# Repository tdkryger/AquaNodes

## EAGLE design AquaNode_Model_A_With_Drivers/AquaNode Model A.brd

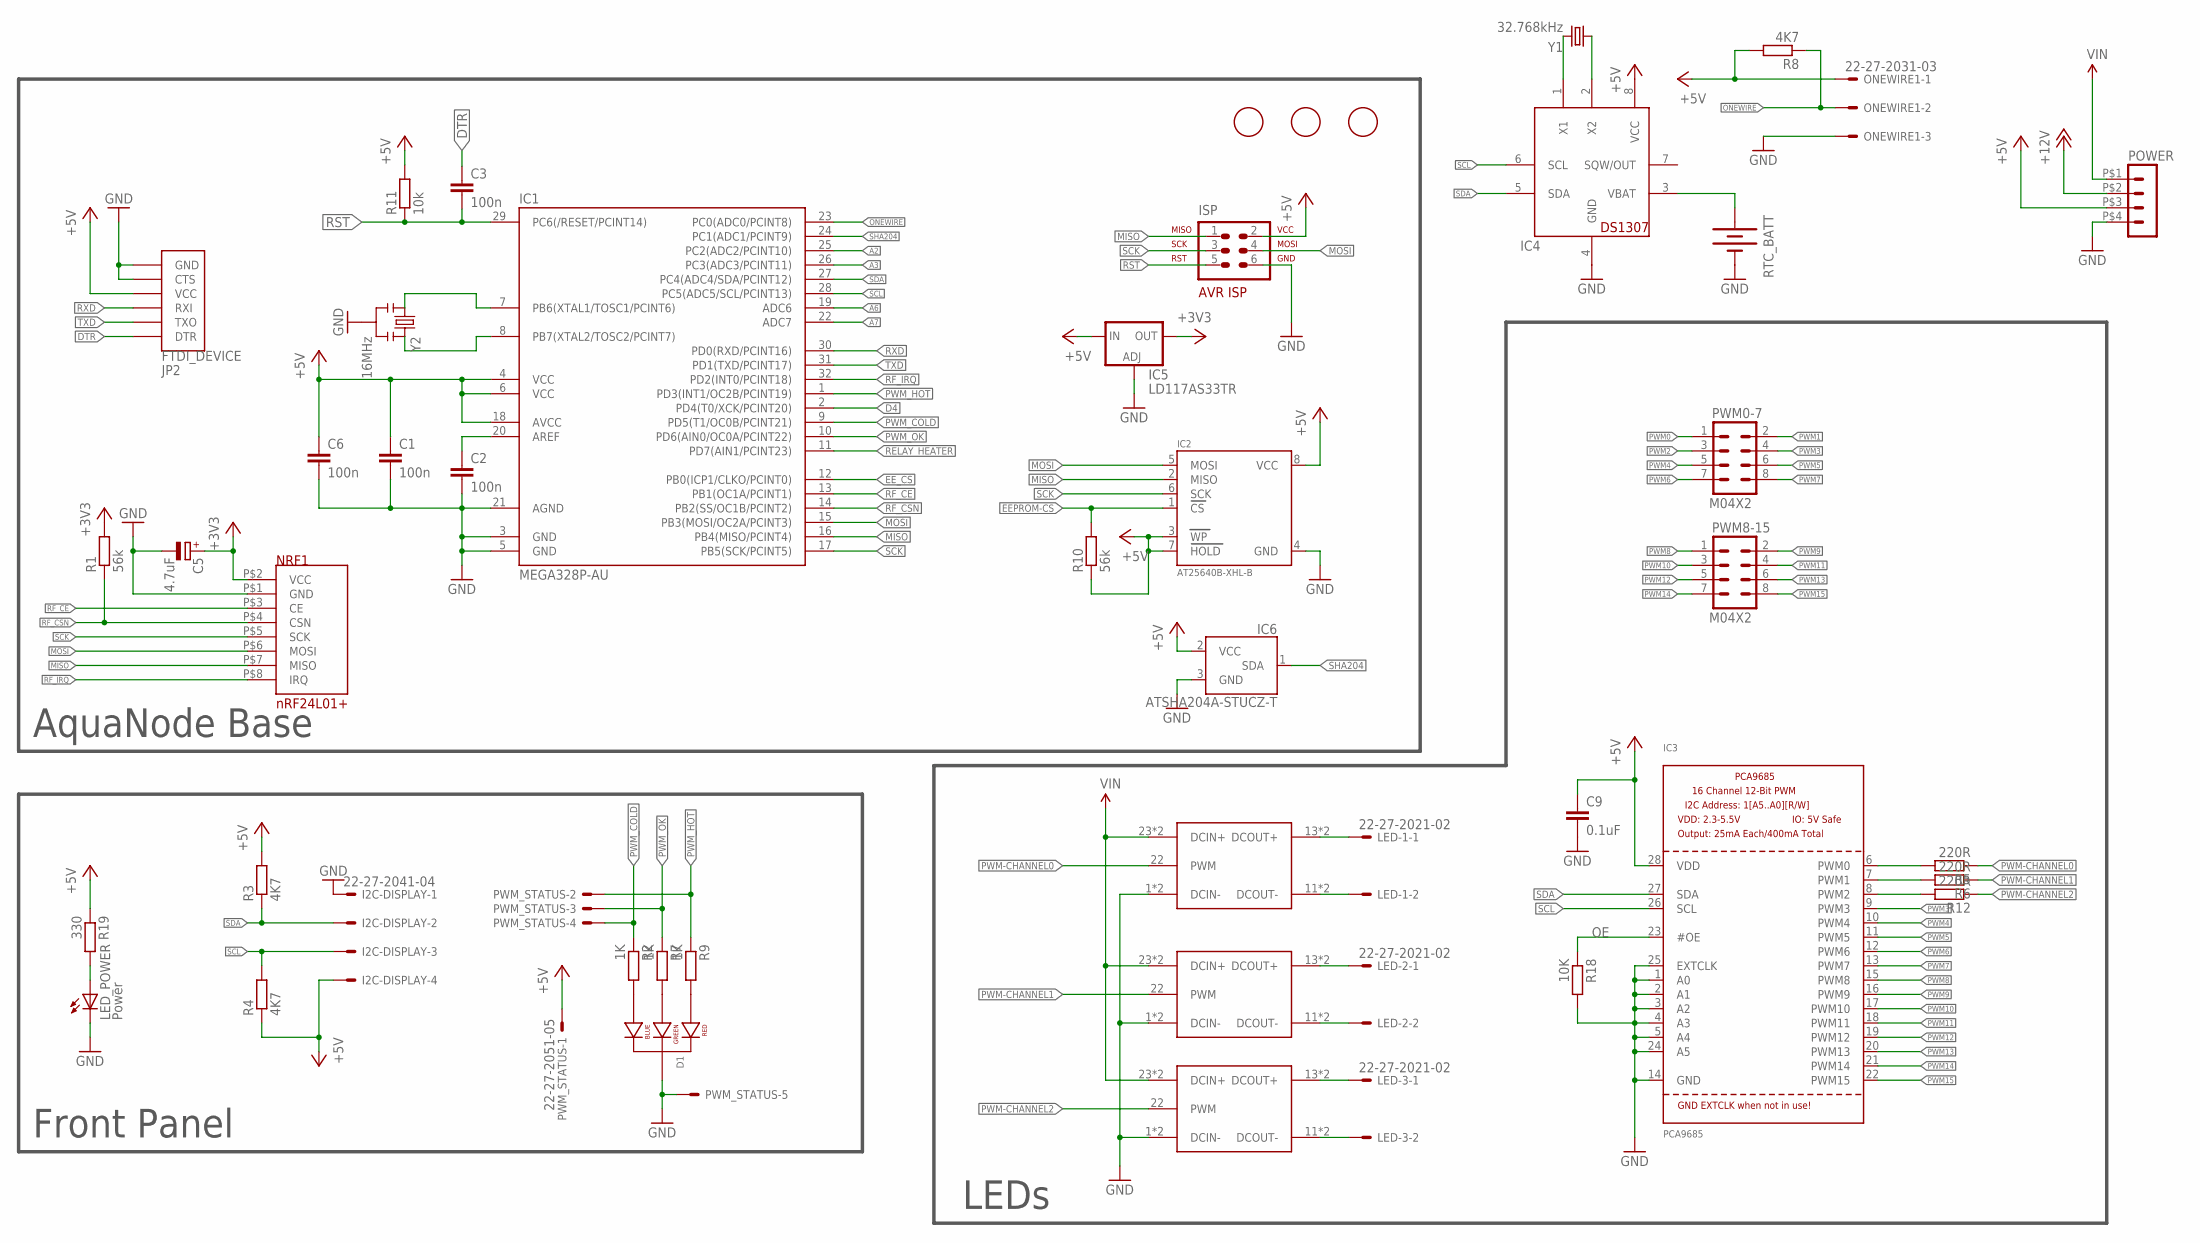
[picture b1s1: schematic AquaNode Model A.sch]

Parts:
C1, C2, C3, C6: 100n; C0603
C5: 4.7uF; E2,5-6
C9: 0.1uF; C0805
D1: LED-RGB-CC; LED-RGB-THRU
DRV1, DRV2, DRV3: DLL-XXXH; LDD_H
FID1, FID2, FID3: FIDUCIAL; FIDUCIAL_1MM
I2C-DISPLAY: 22-27-2041-04; 6410-04
IC1: MEGA328P-AU; TQFP32-08
IC2: AT25640B-XHL-B; TSSOP8-4.4MM
IC3: PCA9685; TSSOP28
IC4: DS1307; SO08
IC5: LD117AS33TR; SOT223
IC6: ATSHA204A-STUCZ-T; SOT23-3
ISP: ISP; AVR-ISP-6
JP2: FTDI_DEVICE; FTDI_DEVICE_SIDE
LED-1, LED-2, LED-3: 22-27-2021-02; 6410-02
LED_POWER: Power; LED3MM
NRF1: NRF24L01+.EBAY
ONEWIRE1: 22-27-2031-03; 6410-03
POWER: HEADER_POS4_43045-0412; 43045-0412
PWM0-7, PWM8-15: M04X2; 2X4
PWM_STATUS: 22-27-2051-05; 6410-05
R1, R10: 56k; M0805
R2, R7, R9: 1K; M0805
R3, R4, R8: 4K7; M0805
R5, R6, R12: 220R; M0805
R11: 10k; R0603
R18: 10K; M0805
R19: 330; M0805
RTC_BATT: BATTERY20SMD; BATTCON_20MM
Y1: 32.768kHz; CRYSTAL-32KHZ-SMD
Y2: 16MHz; RESONATOR-PTH

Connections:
+3V3: C5.+, IC5.4 (OUT), NRF1.P$2 (VCC), R1.2
+5V: C1.1, C6.1, C9.1, I2C-DISPLAY.4, IC1.4 (VCC), IC1.6 (VCC), IC1.18 (AVCC), IC2.3 (WP), IC2.7 (HOLD), IC2.8 (VCC), IC3.28 (VDD), IC4.8 (VCC), IC5.3 (IN), IC6.2 (VCC), ISP.2, JP2.P$4 (VCC), ONEWIRE1.1, POWER.P$3 (3), PWM_STATUS.1, R3.2, R4.1, R8.2, R10.1, R11.2, R19.1
+12V: POWER.P$2 (2)
A2: IC1.25 (PC2(ADC2/PCINT10))
A3: IC1.26 (PC3(ADC3/PCINT11))
A6: IC1.19 (ADC6)
A7: IC1.22 (ADC7)
D4: IC1.2 (PD4(T0/XCK/PCINT20))
DTR: C3.1, JP2.P$1 (DTR)
EEPROM-CS: IC2.1 (CS), R10.2
EE_CS: IC1.12 (PB0(ICP1/CLKO/PCINT0))
GND: C1.2, C2.2, C5.-, C6.2, C9.2, D1.2 (CATHODE), DRV1.1 (DCIN-), DRV1.2 (DCIN-), DRV2.1 (DCIN-), DRV2.2 (DCIN-), DRV3.1 (DCIN-), DRV3.2 (DCIN-), I2C-DISPLAY.1, IC1.3 (GND), IC1.5 (GND), IC1.21 (AGND), IC2.4 (GND), IC3.1 (A0), IC3.2 (A1), IC3.3 (A2), IC3.4 (A3), IC3.5 (A4), IC3.14 (GND), IC3.24 (A5), IC3.25 (EXTCLK), IC4.4 (GND), IC5.1 (ADJ), IC6.3 (GND), ISP.6, JP2.P$5 (CTS), JP2.P$6 (GND), LED_POWER.K (C), NRF1.P$1 (GND), ONEWIRE1.3, POWER.P$4 (4), PWM_STATUS.5, R18.2, RTC_BATT.2 (-), Y2.2
LED+1: DRV1.13 (DCOUT+), DRV1.14 (DCOUT+), LED-1.1
LED+2: DRV2.13 (DCOUT+), DRV2.14 (DCOUT+), LED-2.1
LED+3: DRV3.13 (DCOUT+), DRV3.14 (DCOUT+), LED-3.1
MISO: IC1.16 (PB4(MISO/PCINT4)), IC2.2 (MISO), ISP.1, NRF1.P$7 (MISO)
MOSI: IC1.15 (PB3(MOSI/OC2A/PCINT3)), IC2.5 (MOSI), ISP.4, NRF1.P$6 (MOSI)
unnamed: D1.4 (BLUE_CATHODE), R2.2
unnamed: D1.3 (GREEN_CATHODE), R7.2
unnamed: D1.1 (RED_CATHODE), R9.2
unnamed: C2.1, IC1.20 (AREF)
unnamed: IC4.3 (VBAT), RTC_BATT.1 (+)
unnamed: IC4.1 (X1), Y1.X2 (2)
unnamed: IC4.2 (X2), Y1.X1 (1)
unnamed: IC1.7 (PB6(XTAL1/TOSC1/PCINT6)), Y2.1
unnamed: IC1.8 (PB7(XTAL2/TOSC2/PCINT7)), Y2.3
unnamed: DRV1.11 (DCOUT-), DRV1.12 (DCOUT-), LED-1.2
unnamed: DRV2.11 (DCOUT-), DRV2.12 (DCOUT-), LED-2.2
unnamed: DRV3.11 (DCOUT-), DRV3.12 (DCOUT-), LED-3.2
unnamed: LED_POWER.A, R19.2
OE: IC3.23 (#OE), R18.1
ONEWIRE: IC1.23 (PC0(ADC0/PCINT8)), ONEWIRE1.2, R8.1
PWM0: IC3.6 (PWM0), PWM0-7.1, R5.2
PWM1: IC3.7 (PWM1), PWM0-7.2, R6.2
PWM2: IC3.8 (PWM2), PWM0-7.3, R12.2
PWM3: IC3.9 (PWM3), PWM0-7.4
PWM4: IC3.10 (PWM4), PWM0-7.5
PWM5: IC3.11 (PWM5), PWM0-7.6
PWM6: IC3.12 (PWM6), PWM0-7.7
PWM7: IC3.13 (PWM7), PWM0-7.8
PWM8: IC3.15 (PWM8), PWM8-15.1
PWM9: IC3.16 (PWM9), PWM8-15.2
PWM10: IC3.17 (PWM10), PWM8-15.3
PWM11: IC3.18 (PWM11), PWM8-15.4
PWM12: IC3.19 (PWM12), PWM8-15.5
PWM13: IC3.20 (PWM13), PWM8-15.6
PWM14: IC3.21 (PWM14), PWM8-15.7
PWM15: IC3.22 (PWM15), PWM8-15.8
PWM-CHANNEL0: DRV1.22 (PWM), R5.1
PWM-CHANNEL1: DRV2.22 (PWM), R6.1
PWM-CHANNEL2: DRV3.22 (PWM), R12.1
PWM_COLD: IC1.9 (PD5(T1/OC0B/PCINT21)), PWM_STATUS.4, R2.1
PWM_HOT: IC1.1 (PD3(INT1/OC2B/PCINT19)), PWM_STATUS.2, R9.1
PWM_OK: IC1.10 (PD6(AIN0/OC0A/PCINT22)), PWM_STATUS.3, R7.1
RELAY_HEATER: IC1.11 (PD7(AIN1/PCINT23))
RF_CE: IC1.13 (PB1(OC1A/PCINT1)), NRF1.P$3 (CE)
RF_CSN: IC1.14 (PB2(SS/OC1B/PCINT2)), NRF1.P$4 (CSN), R1.1
RF_IRQ: IC1.32 (PD2(INT0/PCINT18)), NRF1.P$8 (IRQ)
RST: C3.2, IC1.29 (PC6(/RESET/PCINT14)), ISP.5, R11.1
RXD: IC1.30 (PD0(RXD/PCINT16)), JP2.P$3 (RXI)
SCK: IC1.17 (PB5(SCK/PCINT5)), IC2.6 (SCK), ISP.3, NRF1.P$5 (SCK)
SCL: I2C-DISPLAY.3, IC1.28 (PC5(ADC5/SCL/PCINT13)), IC3.26 (SCL), IC4.6 (SCL), R4.2
SDA: I2C-DISPLAY.2, IC1.27 (PC4(ADC4/SDA/PCINT12)), IC3.27 (SDA), IC4.5 (SDA), R3.1
SHA204: IC1.24 (PC1(ADC1/PCINT9)), IC6.1 (SDA)
TXD: IC1.31 (PD1(TXD/PCINT17)), JP2.P$2 (TXO)
VIN: DRV1.23 (DCIN+), DRV1.24 (DCIN+), DRV2.23 (DCIN+), DRV2.24 (DCIN+), DRV3.23 (DCIN+), DRV3.24 (DCIN+), POWER.P$1 (1)

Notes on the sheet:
Front Panel
LEDs
AquaNode Base

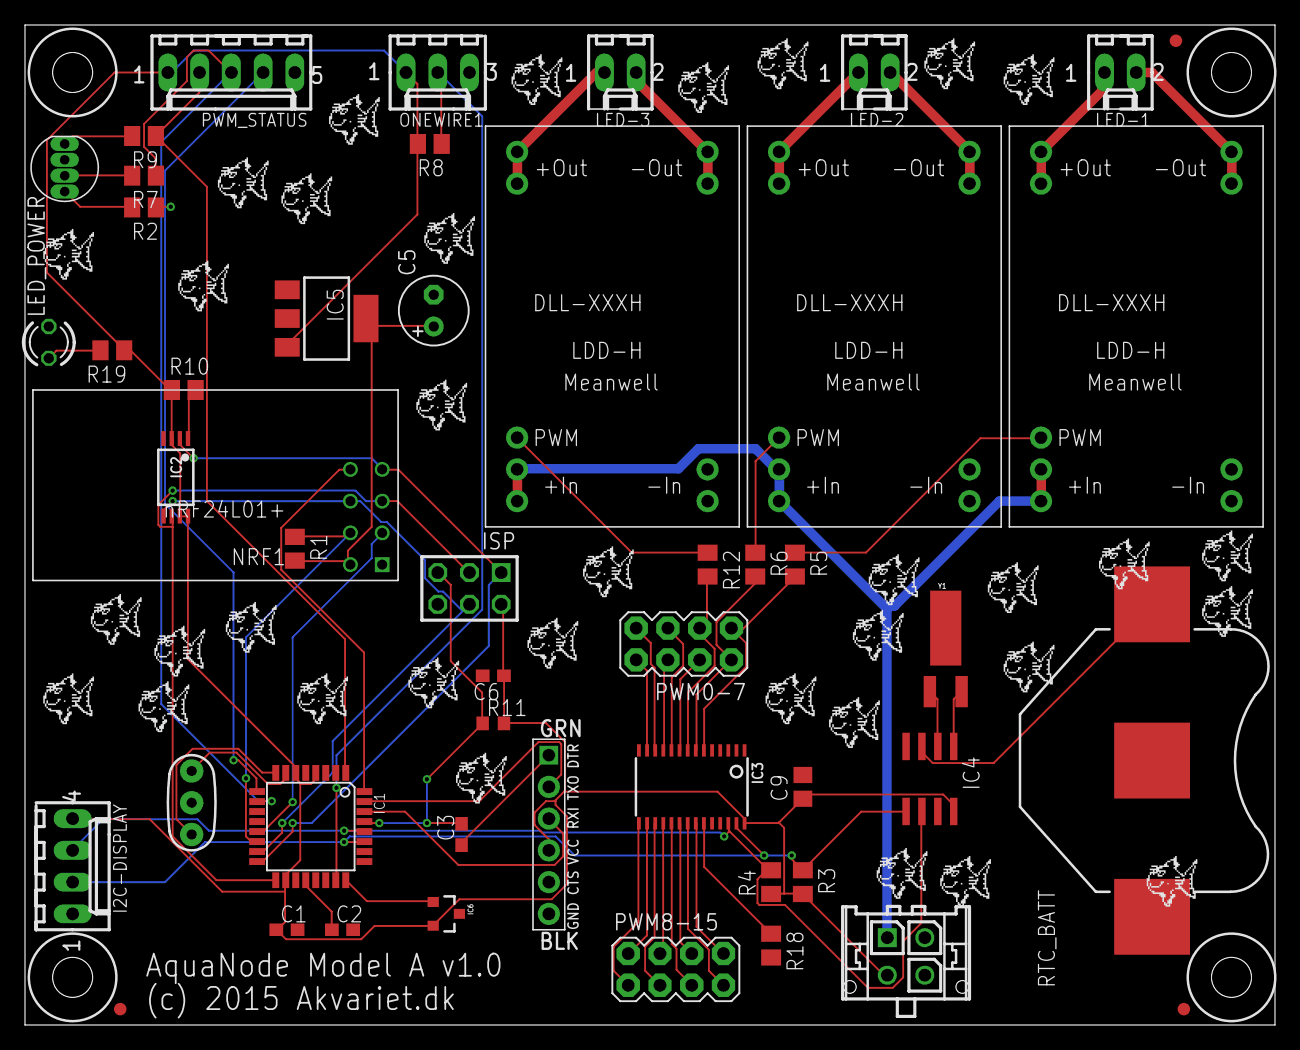
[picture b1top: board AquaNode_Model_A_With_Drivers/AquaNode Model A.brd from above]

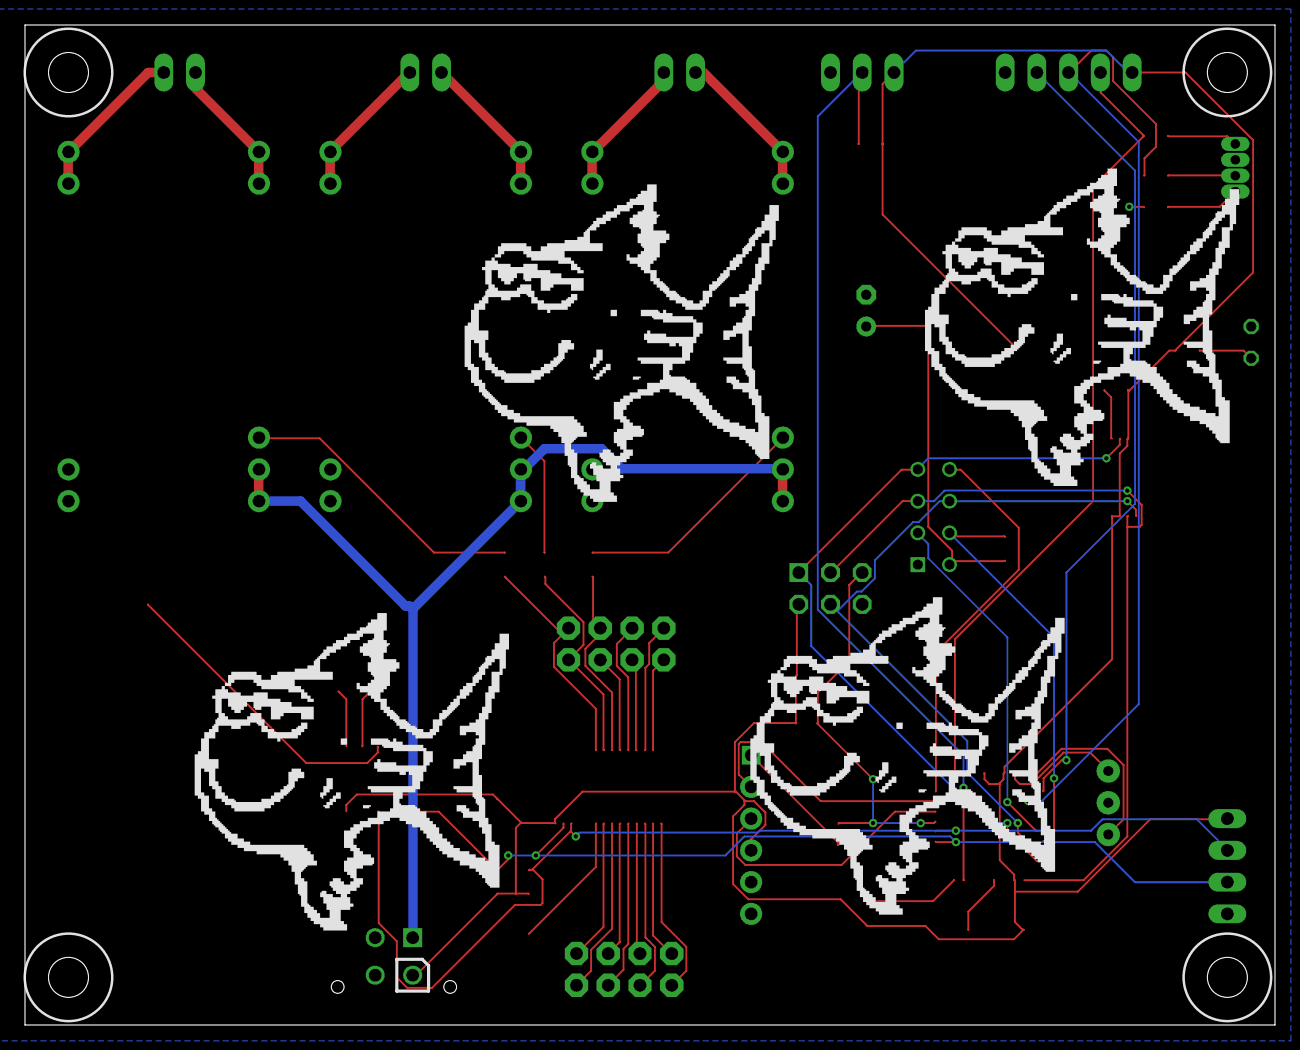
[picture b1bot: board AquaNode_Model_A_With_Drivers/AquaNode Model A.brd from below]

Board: 2 copper layers, 100.0 x 80.0 mm, 91 parts (4 on the bottom side), 58 nets.

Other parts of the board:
U$1, U$2, U$3, U$5, U$8, U$13, U$14, U$15, U$16, U$17, U$18, U$19, U$20, U$21, U$22, U$23, U$24, U$25, U$26, U$27, U$28, U$29, U$30, U$31, U$32, U$33, U$34, U$35, U$36, U$37, U$38, U$39, U$40, U$41: THEFISH_SMALL
U$4, U$6, U$7, U$42: HOLE3.2
U$9, U$10, U$11, U$12: THEFISH

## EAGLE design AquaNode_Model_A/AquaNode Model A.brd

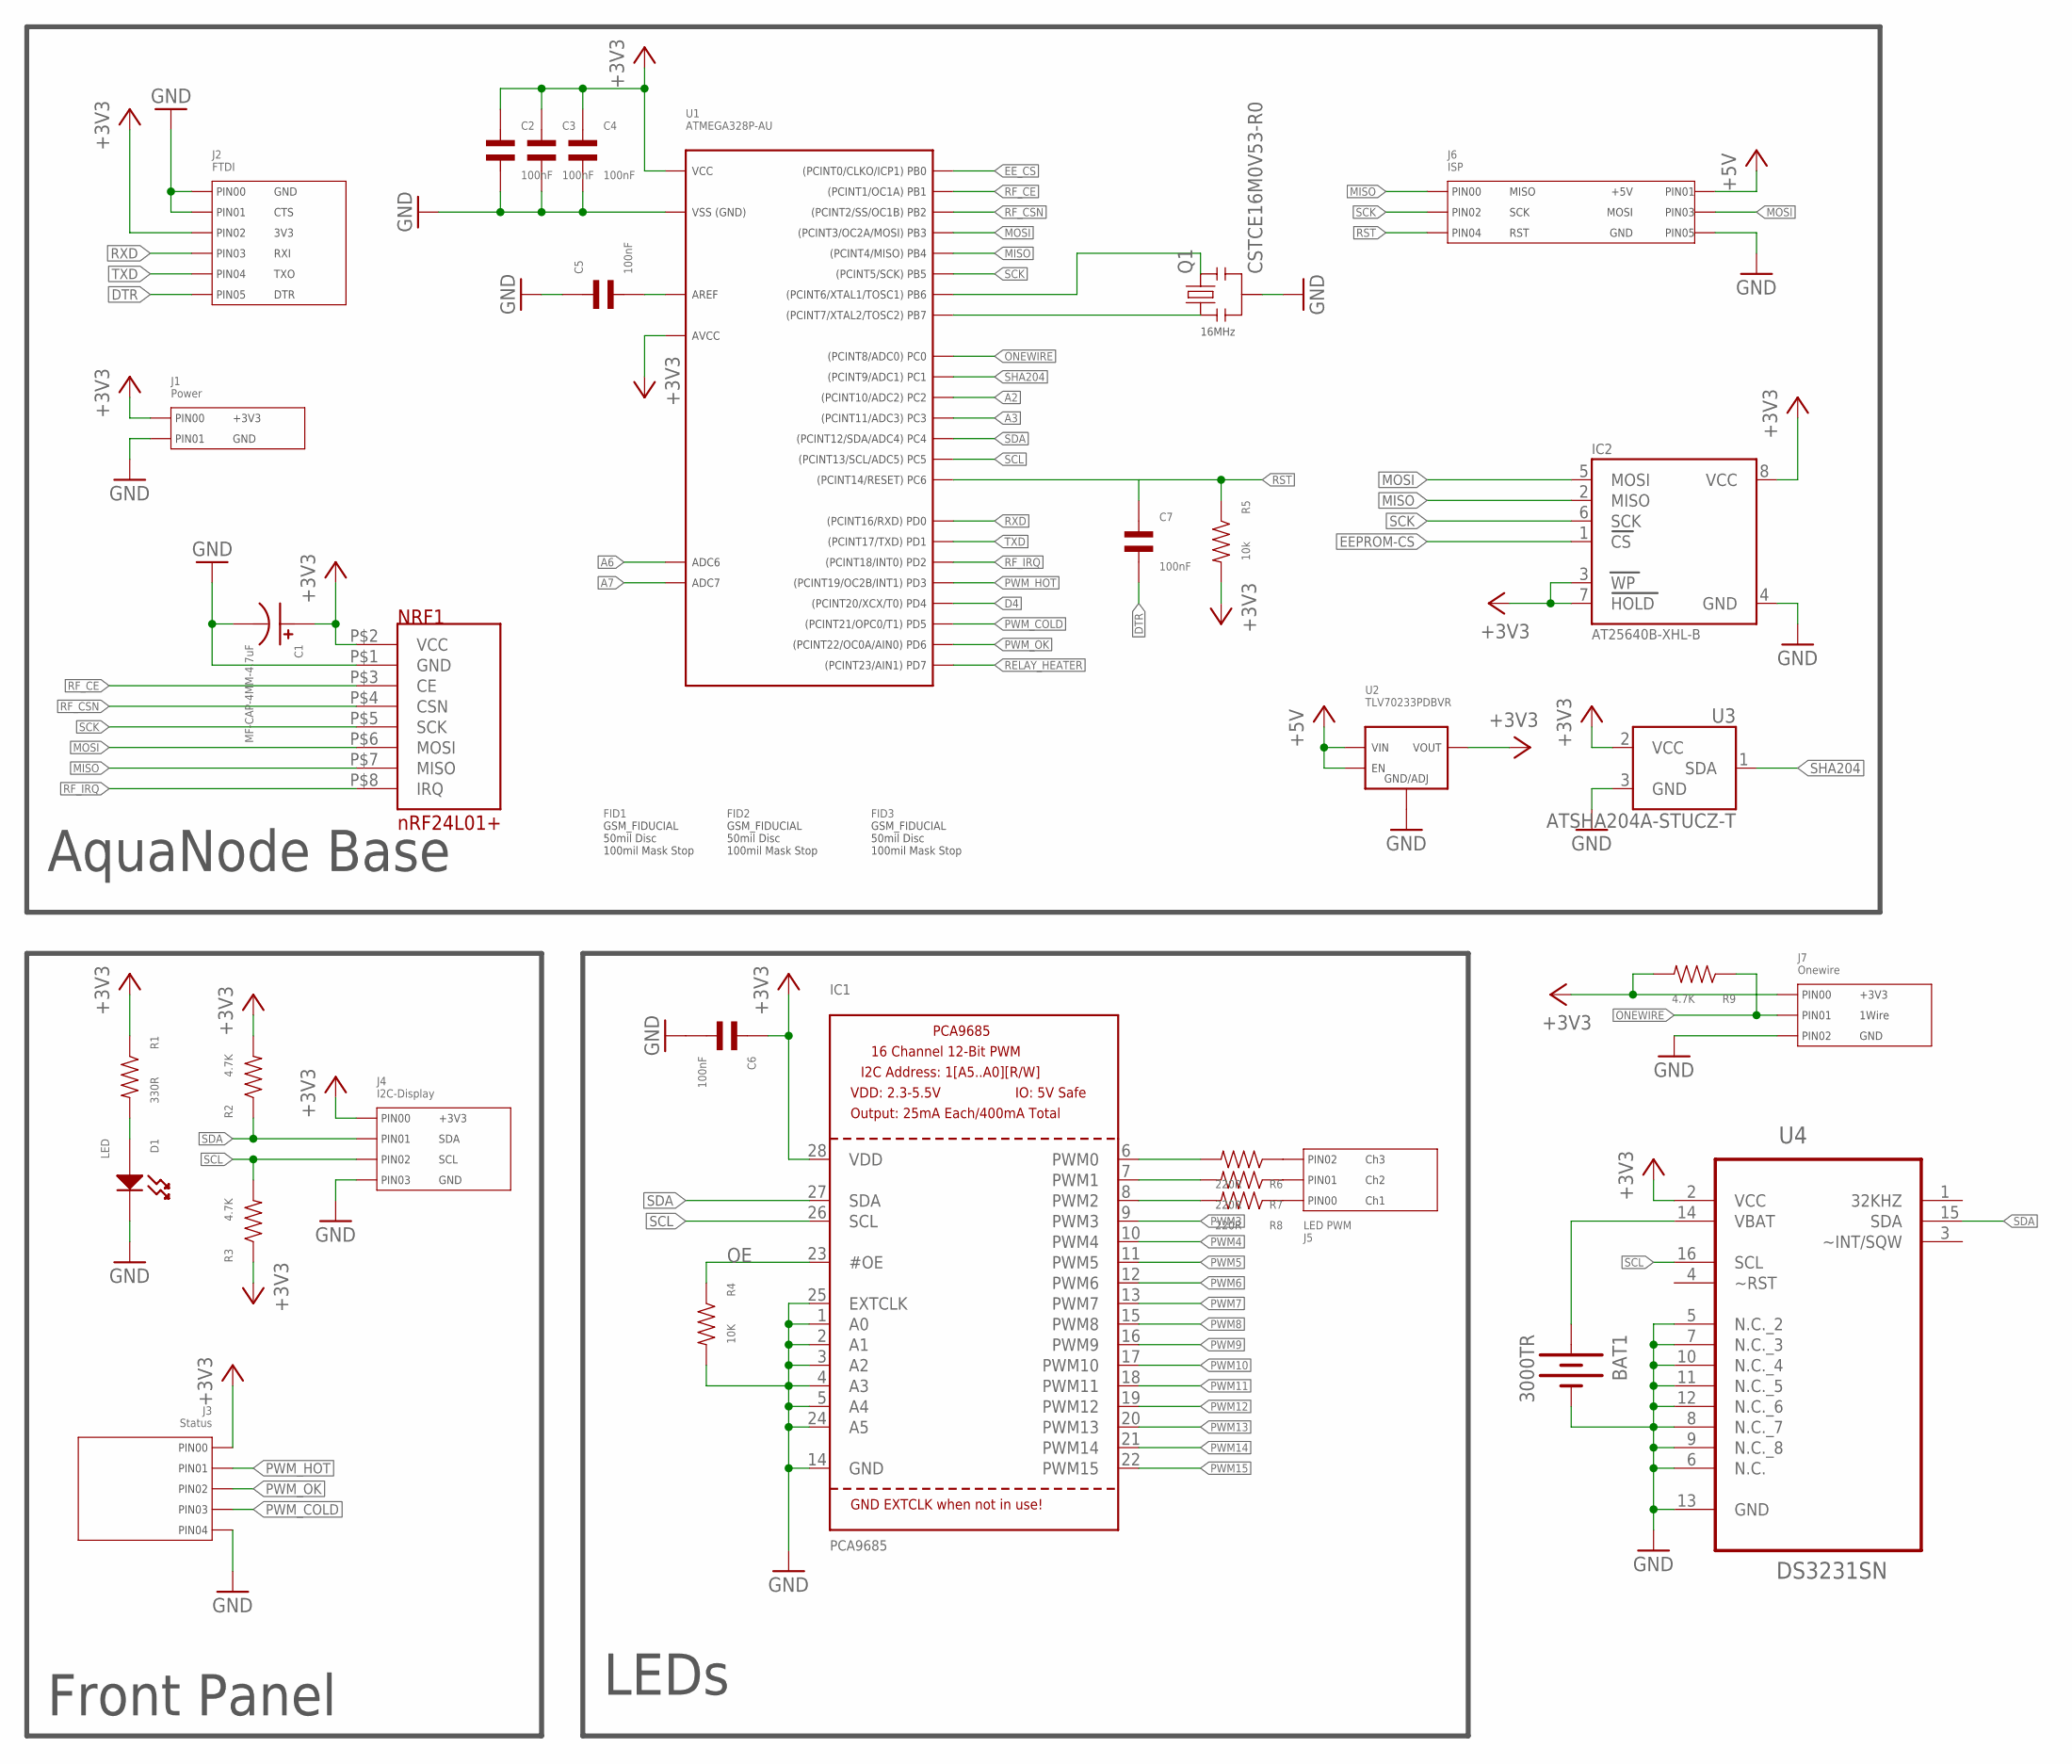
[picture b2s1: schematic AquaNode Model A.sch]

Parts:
BAT1: 3000TR; BATTCON_12MM
C1: MF-CAP-4MM-4.7uF; CP4MM
C2, C3, C4, C5, C6, C7: 100nF; C0603
D1: LED; LED0805
FID1, FID2, FID3: GSM_FIDUCIAL
IC1: PCA9685; TSSOP28
IC2: AT25640B-XHL-B; TSSOP8-4.4MM
J1: Power; PTH_2.54MM_01X02
J2: FTDI; PTH_2.54MM_01X06
J3: Status; PTH_2.54MM_01X05
J4: I2C-Display; PTH_2.54MM_01X04
J5: LED PWM; PTH_2.54MM_01X03
J6: ISP; PTH_2.54MM_02X03
J7: Onewire; PTH_2.54MM_01X03
NRF1: 4Fx2-254mm; NRF24L01+.EBAY
Q1: CSTCE16M0V53-R0; RESONATOR-SMD
R1: 330R; R0603
R2, R3, R9: 4.7K; R0603
R4: 10K; R0603
R5: 10k; R0603
R6, R7, R8: 220R; R0603
U1: ATMEGA328P-AU; TQFP32
U2: TLV70233PDBVR; SOT-23-5
U3: ATSHA204A-STUCZ-T; SOT23-3
U4: DS3231SN; SOIC127P1032X265-16N

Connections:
+3V3: C1.P$1, C2.P$1, C3.P$1, C4.P$1, C6.P$1, IC1.28 (VDD), IC2.3 (WP), IC2.7 (HOLD), IC2.8 (VCC), J1.P$2 (PIN0), J2.P$3 (PIN2), J3.P$1 (PIN0), J4.P$1 (PIN0), J7.P$1 (PIN0), NRF1.P$2 (VCC), R1.P$1, R2.P$2, R3.P$1, R5.P$2, R9.P$2, U1.P$4 (VCC), U1.P$6 (VCC), U1.P$18 (AVCC), U2.P$5 (VOUT), U3.2 (VCC), U4.2 (VCC)
+5V: J6.P$2 (PIN1), U2.P$1 (VIN), U2.P$3 (EN)
A2: U1.P$25 (PC2)
A3: U1.P$26 (PC3)
A6: U1.P$19 (ADC6)
A7: U1.P$22 (ADC7)
D4: U1.P$2 (PD4)
DTR: C7.P$2, J2.P$6 (PIN5)
EEPROM-CS: IC2.1 (CS)
EE_CS: U1.P$12 (PB0)
GND: BAT1.GND (-), C1.P$2, C2.P$2, C3.P$2, C4.P$2, C5.P$1, C6.P$2, D1.CATHODE, IC1.1 (A0), IC1.2 (A1), IC1.3 (A2), IC1.4 (A3), IC1.5 (A4), IC1.14 (GND), IC1.24 (A5), IC1.25 (EXTCLK), IC2.4 (GND), J1.P$1 (PIN1), J2.P$1 (PIN0), J2.P$2 (PIN1), J3.P$5 (PIN4), J4.P$4 (PIN3), J6.P$6 (PIN5), J7.P$3 (PIN2), NRF1.P$1 (GND), Q1.2, R4.P$2, U1.P$3 (GND), U1.P$5 (GND), U1.P$21 (GND), U2.P$2 (GND/ADJ), U3.3 (GND), U4.5 (N.C._2), U4.6 (N.C.), U4.7 (N.C._3), U4.8 (N.C._7), U4.9 (N.C._8), U4.10 (N.C._4), U4.11 (N.C._5), U4.12 (N.C._6), U4.13 (GND)
MISO: IC2.2 (MISO), J6.P$1 (PIN0), NRF1.P$7 (MISO), U1.P$16 (PB4)
MOSI: IC2.5 (MOSI), J6.P$4 (PIN3), NRF1.P$6 (MOSI), U1.P$15 (PB3)
unnamed: D1.ANODE, R1.P$2
unnamed: J5.P$3 (PIN2), R6.P$1
unnamed: J5.P$2 (PIN1), R7.P$1
unnamed: C5.P$2, U1.P$20 (AREF)
unnamed: BAT1.PWR@1 (+), U4.14 (VBAT)
unnamed: J5.P$1 (PIN0), R8.P$1
unnamed: Q1.3, U1.P$7 (PB6)
unnamed: Q1.1, U1.P$8 (PB7)
OE: IC1.23 (#OE), R4.P$1
ONEWIRE: J7.P$2 (PIN1), R9.P$1, U1.P$23 (PC0)
PWM0: IC1.6 (PWM0), R6.P$2
PWM1: IC1.7 (PWM1), R7.P$2
PWM2: IC1.8 (PWM2), R8.P$2
PWM3: IC1.9 (PWM3)
PWM4: IC1.10 (PWM4)
PWM5: IC1.11 (PWM5)
PWM6: IC1.12 (PWM6)
PWM7: IC1.13 (PWM7)
PWM8: IC1.15 (PWM8)
PWM9: IC1.16 (PWM9)
PWM10: IC1.17 (PWM10)
PWM11: IC1.18 (PWM11)
PWM12: IC1.19 (PWM12)
PWM13: IC1.20 (PWM13)
PWM14: IC1.21 (PWM14)
PWM15: IC1.22 (PWM15)
PWM_COLD: J3.P$4 (PIN3), U1.P$9 (PD5)
PWM_HOT: J3.P$2 (PIN1), U1.P$1 (PD3)
PWM_OK: J3.P$3 (PIN2), U1.P$10 (PD6)
RELAY_HEATER: U1.P$11 (PD7)
RF_CE: NRF1.P$3 (CE), U1.P$13 (PB1)
RF_CSN: NRF1.P$4 (CSN), U1.P$14 (PB2)
RF_IRQ: NRF1.P$8 (IRQ), U1.P$32 (PD2)
RST: C7.P$1, J6.P$5 (PIN4), R5.P$1, U1.P$29 (PC6)
RXD: J2.P$4 (PIN3), U1.P$30 (PD0)
SCK: IC2.6 (SCK), J6.P$3 (PIN2), NRF1.P$5 (SCK), U1.P$17 (PB5)
SCL: IC1.26 (SCL), J4.P$3 (PIN2), R3.P$2, U1.P$28 (PC5), U4.16 (SCL)
SDA: IC1.27 (SDA), J4.P$2 (PIN1), R2.P$1, U1.P$27 (PC4), U4.15 (SDA)
SHA204: U1.P$24 (PC1), U3.1 (SDA)
TXD: J2.P$5 (PIN4), U1.P$31 (PD1)

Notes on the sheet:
Front Panel
LEDs
AquaNode Base
16MHz

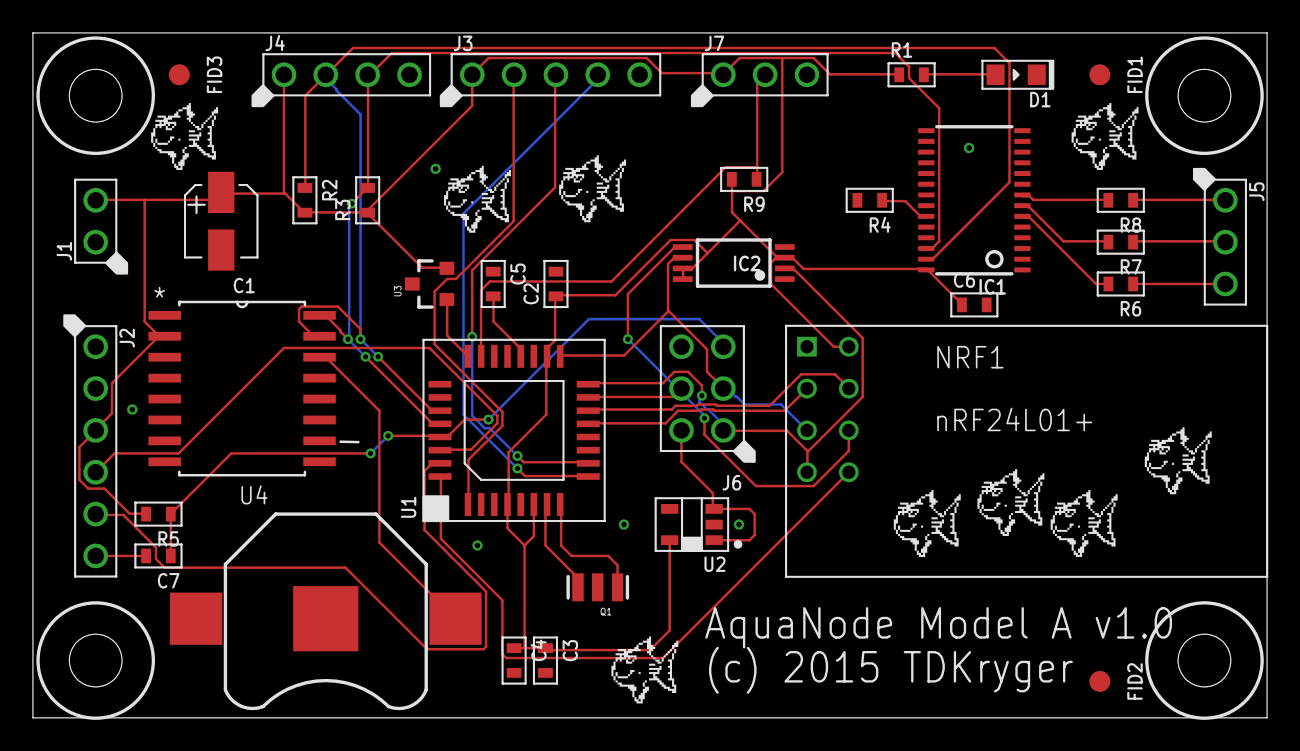
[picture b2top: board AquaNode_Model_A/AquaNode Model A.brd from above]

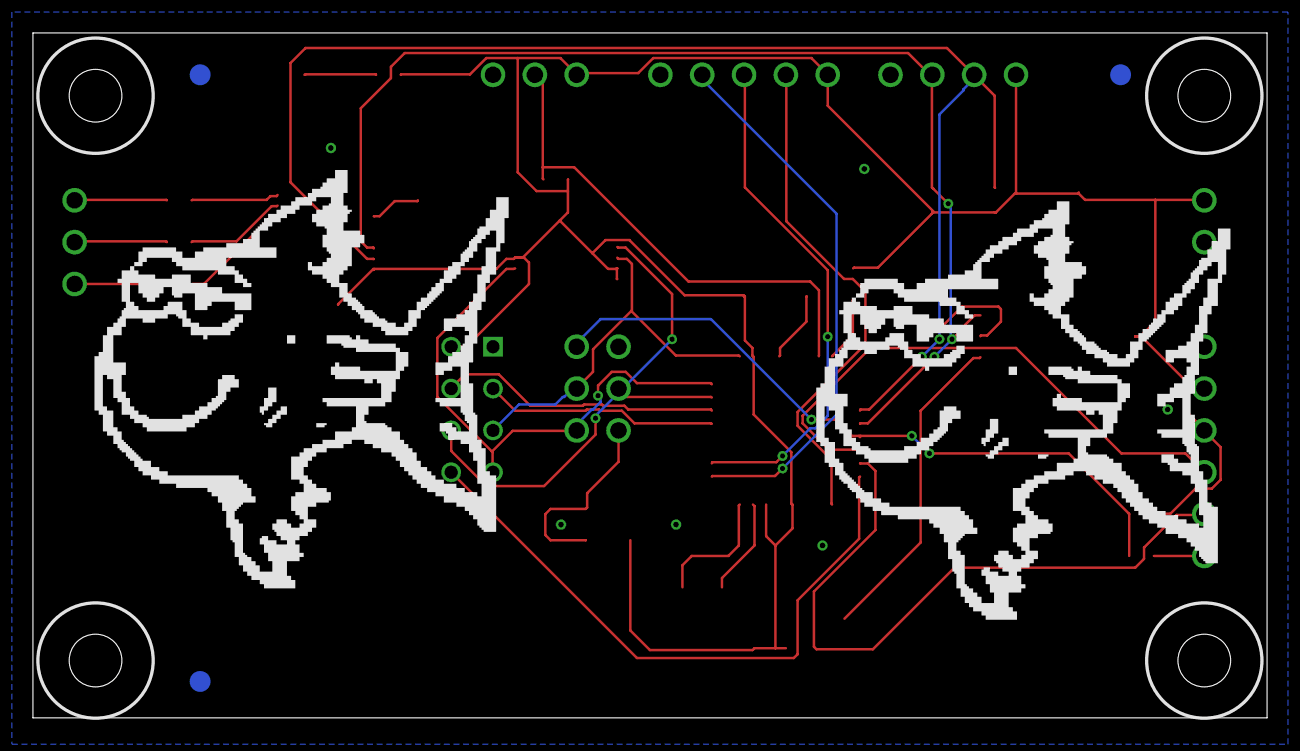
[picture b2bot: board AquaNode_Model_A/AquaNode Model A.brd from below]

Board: 2 copper layers, 74.9 x 41.6 mm, 51 parts (2 on the bottom side), 32 nets.

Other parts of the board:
U$1, U$2, U$3, U$4: HOLE3.2
U$5, U$6, U$7, U$10, U$11, U$12, U$13, U$14, U$15: THEFISH_SMALL
U$8, U$9: THEFISH

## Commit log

2015-08-18 :confetti_ball: Added .gitattributes & .gitignore files

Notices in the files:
AquaNode_Model_A/AquaNode Model A.brd:
(c) 2015 TDKryger
AquaNode_Model_A_With_Drivers/AquaNode Model A.brd:
(c) 2015 Akvariet.dk
parts and their libraries:
microbuilder: This work is placed in the public domain, and may be freely used for commercial and non-commercial work with the following conditions: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
SparkFun-DigitalIC: Licensing: CC v3.0 Share-Alike You are welcome to use this library for commercial purposes.
